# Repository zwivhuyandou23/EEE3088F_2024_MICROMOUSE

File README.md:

# Welcome to the EEE3088F_2024_MICROMOUSE hardware project

## Name
 2024 Micromouse Project

## Description
The Micromouse Project is a maze-solving robot project designed for the EEE3088F 2024 course. Students will focus on designing and manufacturing sensor and power modules for the micro-mouse, meeting specific project requirements while adhering to a strict budget.

## Features
- Sensor module for detecting obstacles
- Power module for powering the entire system
- Integration with provided motherboard and processor boards

## Project Scenarios
Maze completion.

## Usage
The Micromouse project is intended for educational purposes in the EEE3088F 2024 course. Zwivhuya Ndou and Innocent Makhubela worked on designing, manufacturing, and demonstrating the sensor and power modules for the micro-mouse robot.

## Installation
To access some of the contents on the repo you will need kicad to open the project PCB, Schematics designs and an IDE that supports C programming

## Authors and acknowledgment
Zwivhuya Ndou, Innocent Makhubela

## Contributing

Contributions to the ENVIRO-SENSING-HAT project are welcome! If you have any ideas, bug fixes, or improvements, please follow the guidelines outlined in the [CONTRIBUTING.md](CONTRIBUTING.md) file.

## License

The ENVIRO-SENSING-HAT project is licensed under the MIT License. See the [LICENSE](LICENSE.md) file for more information.

## Project status
Ongoing - part of the EEE3088F 2024 course project, to be carried to the second semester course.

## Contact
If you have any questions or inquiries about the Micromouse project, feel free to contact us at Zwivhuya Ndou(ndxzwi002@myuct.ac.za), Innocent Makhubela ().

Thank you for your interest in the Micromouse project!

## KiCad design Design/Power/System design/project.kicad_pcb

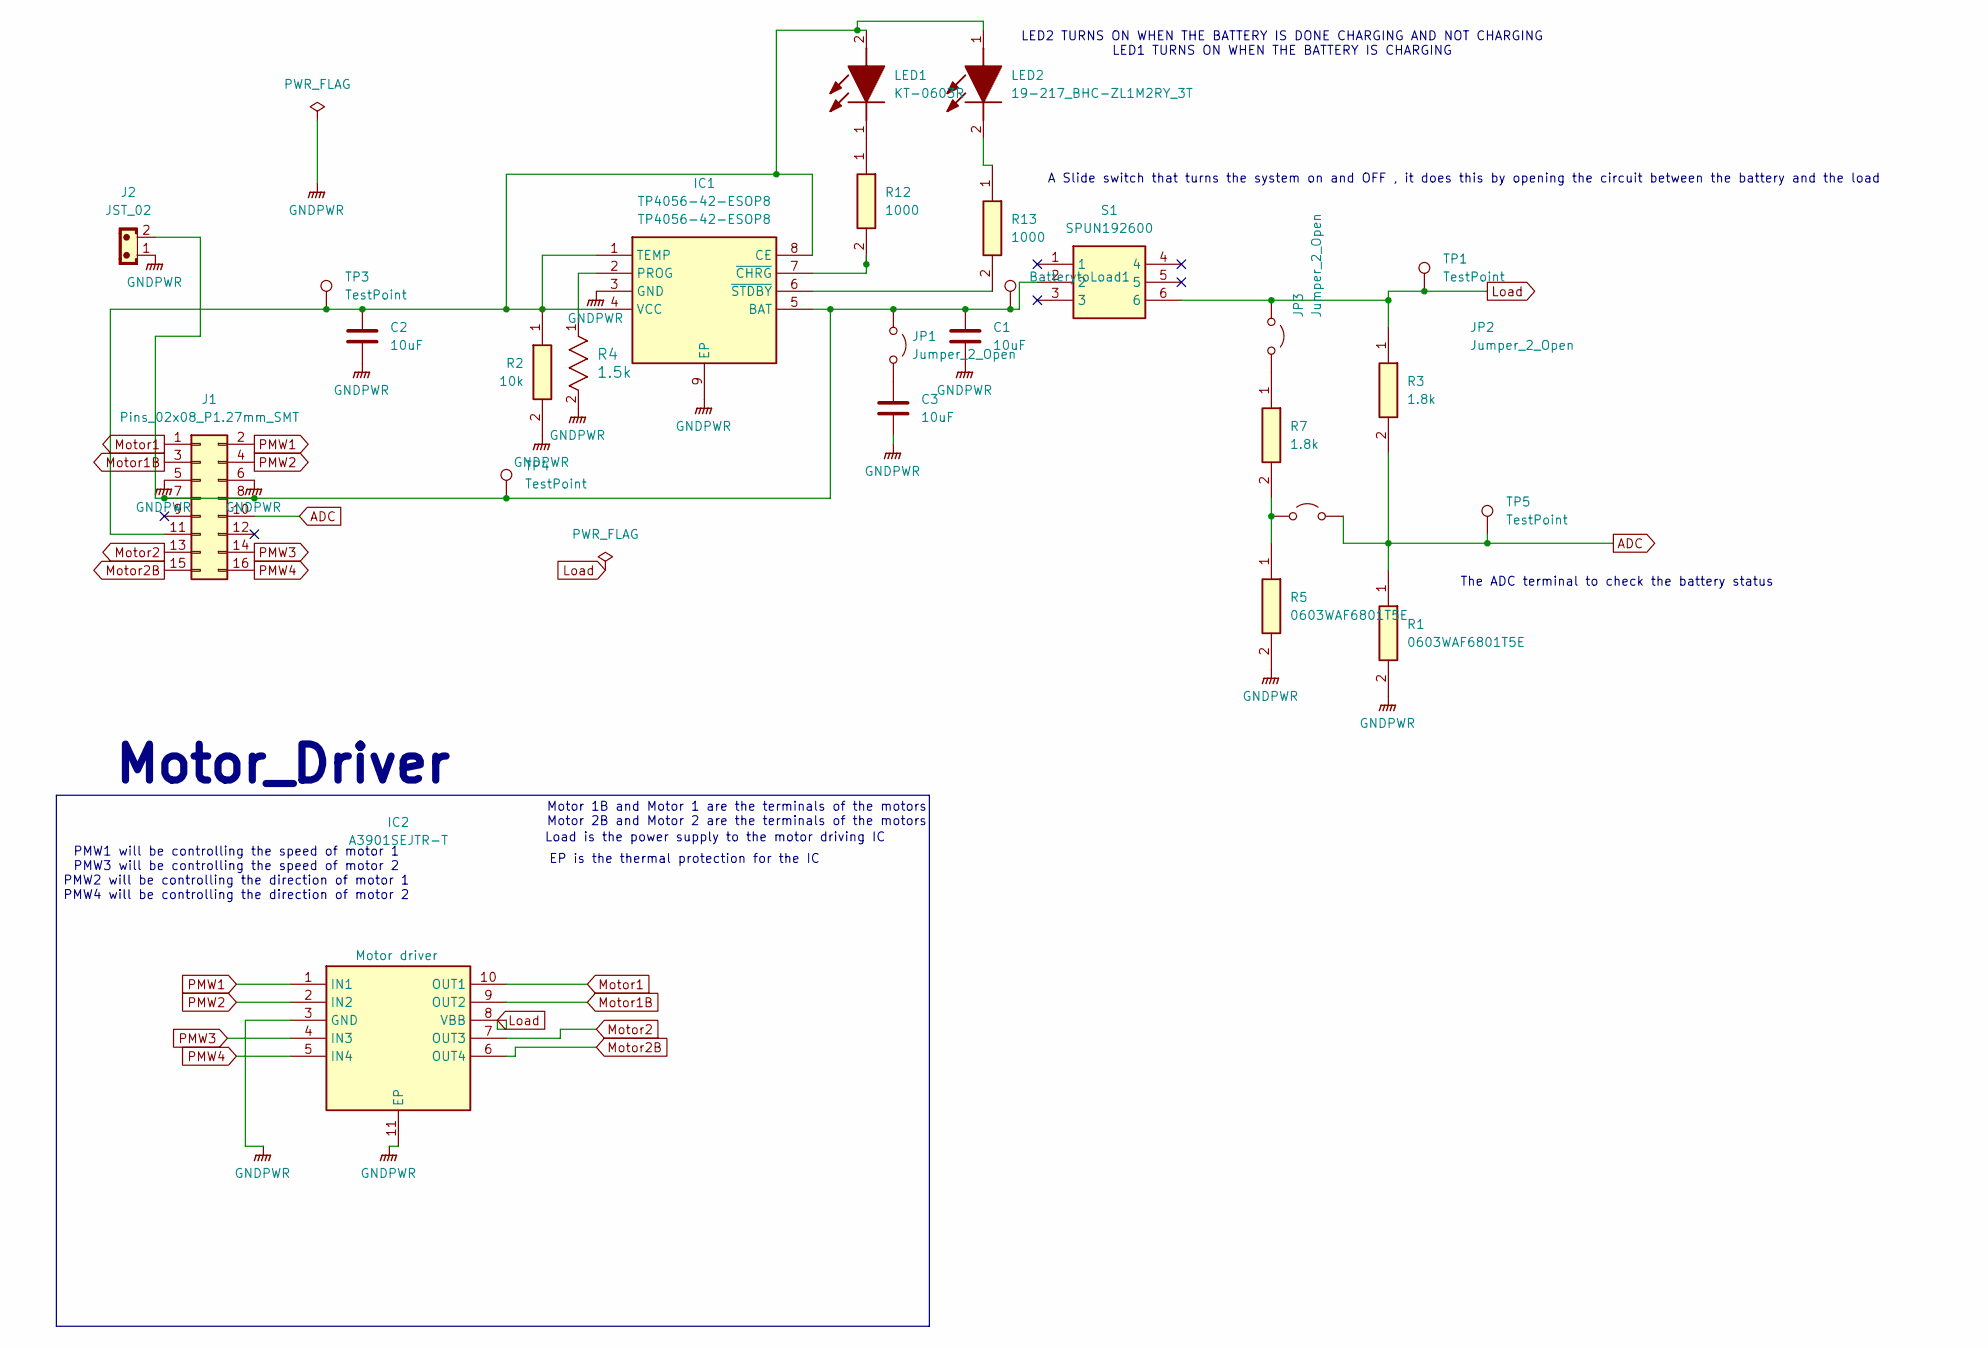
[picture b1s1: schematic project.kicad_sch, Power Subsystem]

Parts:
BatterytoLoad1: TestPoint; TestPoint_Pad_04
C1, C2, C3: 10uF; CAPC1005X70N
IC1: TP4056-42-ESOP8; SOIC127P600X175-9N; Manufacturer_Part_Number TP4056-42-ESOP8
IC2: A3901SEJTR-T; SON50P300X300X75-11N-D; Manufacturer_Part_Number A3901SEJTR-T; Mouser Part Number Motor driver
J1: Pins_02x08_P1.27mm_SMT; PinHeader_2x08_P2.54mm_Vertical; Part Number FTSH-108-01-F-DV
J2: JST_02; JST_JWPF_B02B-JWPF-SK-R_1x02_P2.00mm_Vertical
JP1, JP2, JP3: Jumper_2_Open; SolderJumper-2_P1.3mm_Open_RoundedPad1.0x1.5mm
LED1: KT-0603R; LEDC1608X70N; Manufacturer_Part_Number KT-0603R
LED2: 19-217_BHC-ZL1M2RY_3T; 19217BHCZL1M2RY3T; Manufacturer_Part_Number 19-217/BHC-ZL1M2RY/3T
R1, R5: 0603WAF6801T5E; RESC1608X55N; Manufacturer_Part_Number 0603WAF6801T5E
R2: 10k; RESC3116X65N; Manufacturer_Part_Number 1206W4F1002T5E
R3, R7: 1.8k; RESC1608X55N; Manufacturer_Part_Number 0603WAF1801T5E
R4: 1.5k; RES_8F1001T5E_UNR
R12: 1000; RESC1608X55N; Manufacturer_Part_Number 0603WAF1001T5E
R13: 1000; SOT95P280X145-5N; Manufacturer_Part_Number 0603WAF1001T5E
S1: SPUN192600; Manufacturer_Part_Number SPUN192600; Mouser Part Number 688-SPUN192600
TP1, TP3, TP4, TP5: TestPoint; TestPoint_Pad_04

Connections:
ADC: J1.10 (GND), JP3.2 (B), R1.1, R3.2, TP5.1; also elsewhere on the board
GNDPWR: C1.2, C2.2, C3.2, IC1.3 (GND), IC1.9 (EP), IC2.3 (GND), IC2.11 (EP), J1.5 (+12V), J1.6, J2.1, R1.2, R2.2, R4.2, R5.2
Load: IC2.8 (VBB), JP2.1 (A), R3.1, S1.6, TP1.1
Motor1: IC2.10 (OUT1), J1.1
Motor1B: IC2.9 (OUT2), J1.3
Motor2: IC2.7 (OUT3), J1.13 (-12)
Motor2B: IC2.6 (OUT4), J1.15 (-12V)
unnamed: BatterytoLoad1.1, C1.1, IC1.5 (BAT), J1.7 (12V), J1.8 (+12V), J2.2, JP1.1 (A), S1.2, TP4.1
unnamed 8: C2.1, IC1.1 (TEMP), IC1.4 (VCC), IC1.8 (CE), J1.11 (GND), LED1.2 (A), LED2.1 (A), R2.1, TP3.1; also elsewhere on the board
unnamed: IC1.2 (PROG), R4.1
unnamed: IC1.7 (~CHRG), R12.2
unnamed: IC1.6 (~STDBY), R13.2
unnamed: C3.1, JP1.2 (B)
unnamed: JP2.2 (B), R7.1
unnamed: JP3.1 (A), R5.1, R7.2
unnamed: LED1.1 (K), R12.1
unnamed: LED2.2 (K), R13.1
PMW1: IC2.1 (IN1), J1.2
PMW2: IC2.2 (IN2), J1.4
PMW3: IC2.4 (IN3), J1.14 (-12V)
PMW4: IC2.5 (IN4), J1.16

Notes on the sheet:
Motor 1B and Motor 1 are the terminals of the motors
PMW1 will be controlling the speed of motor 1 PMW3 will be controlling the speed of motor 2 PMW2 will be controlling the direction of motor 1 PMW4 will be controlling the direction of motor 2
The ADC terminal to check the battery status
Motor_Driver
Motor 2B and Motor 2 are the terminals of the motors
Load is the power supply to the motor driving IC
LED2 TURNS ON WHEN THE BATTERY IS DONE CHARGING AND NOT CHARGING LED1 TURNS ON WHEN THE BATTERY IS CHARGING
A Slide switch that turns the system on and OFF , it does this by opening the circuit between the battery and the load
EP is the thermal protection for the IC

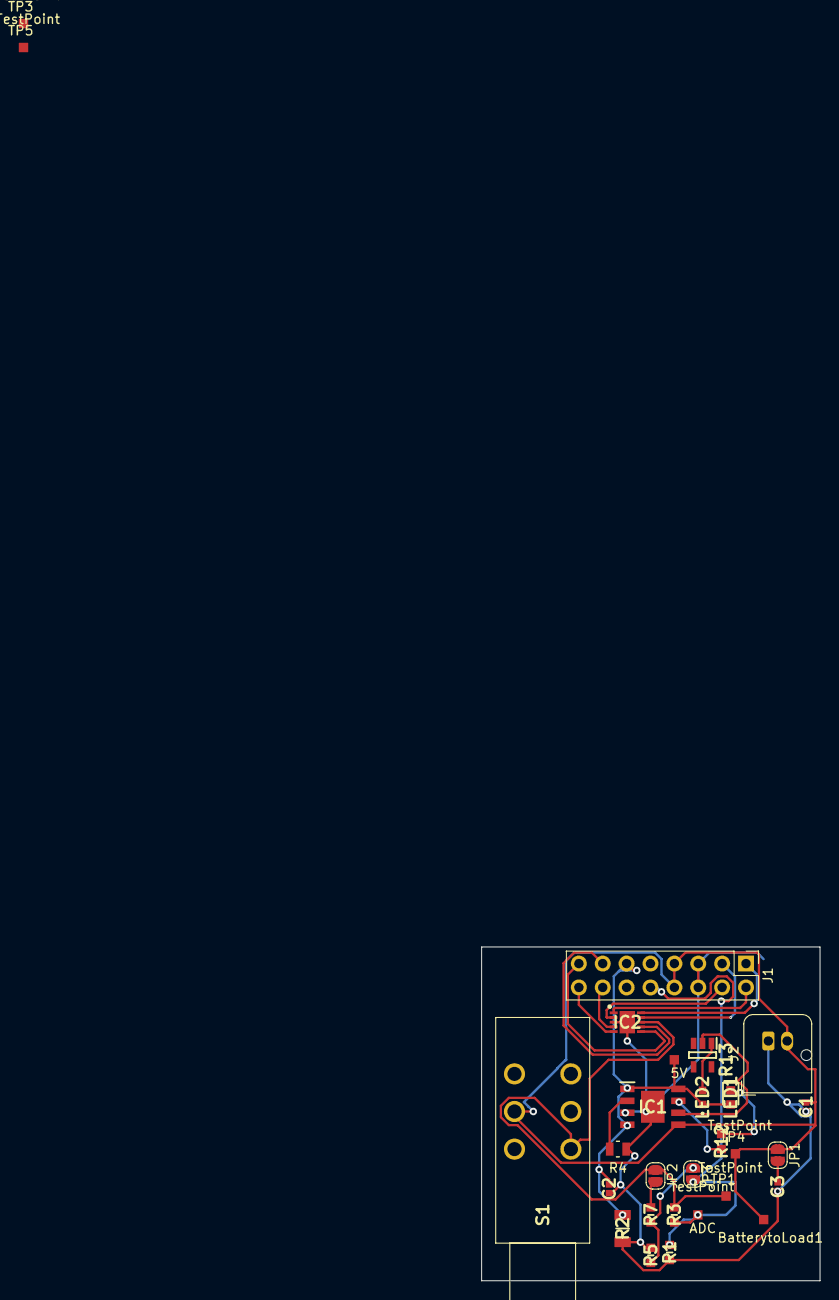
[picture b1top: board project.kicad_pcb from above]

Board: 2 copper layers, 36.0 x 35.5 mm, 28 parts (0 on the bottom side), 21 nets.

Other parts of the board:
5V: TestPoint; TestPoint_Pad_04
ADC: TestPoint; TestPoint_Pad_04

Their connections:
ADC: ADC.1; also elsewhere on the board
unnamed 8: 5V.1; also elsewhere on the board

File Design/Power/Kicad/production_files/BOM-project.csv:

Comment,Designator,Footprint,LCSC;
SPUN192600,S1,SPUN192600,;
A3901SEJTR-T,IC2,SON50P300X300X75-11N-D,;
19-217_BHC-ZL1M2RY_3T,LED2,19217BHCZL1M2RY3T,;
KT-0603R,LED1,LEDC1608X70N,;
TP4056-42-ESOP8,IC1,SOIC127P600X175-9N,;
1000,R13,0603WAF1001TSE,;0603WAF1001TSE,
1000,R12,0603WAF1001TSE,;0603WAF1001TSE,
1.5k,R4,RES_8F1001T5E_UNR,;
0603WAF6801T5E,R5,RESC1608X55N,;
10uF,C2,CAPC1005X70N,;
1.8k,R7,RESC1608X55N,;
10uF,C3,CAPC1005X70N,;
10uF,C1,CAPC1005X70N,;
1.8k,R3,RESC1608X55N,;
10k,R2,RESC3116X65N,;
0603WAF6801T5E,R1,RESC1608X55N,;

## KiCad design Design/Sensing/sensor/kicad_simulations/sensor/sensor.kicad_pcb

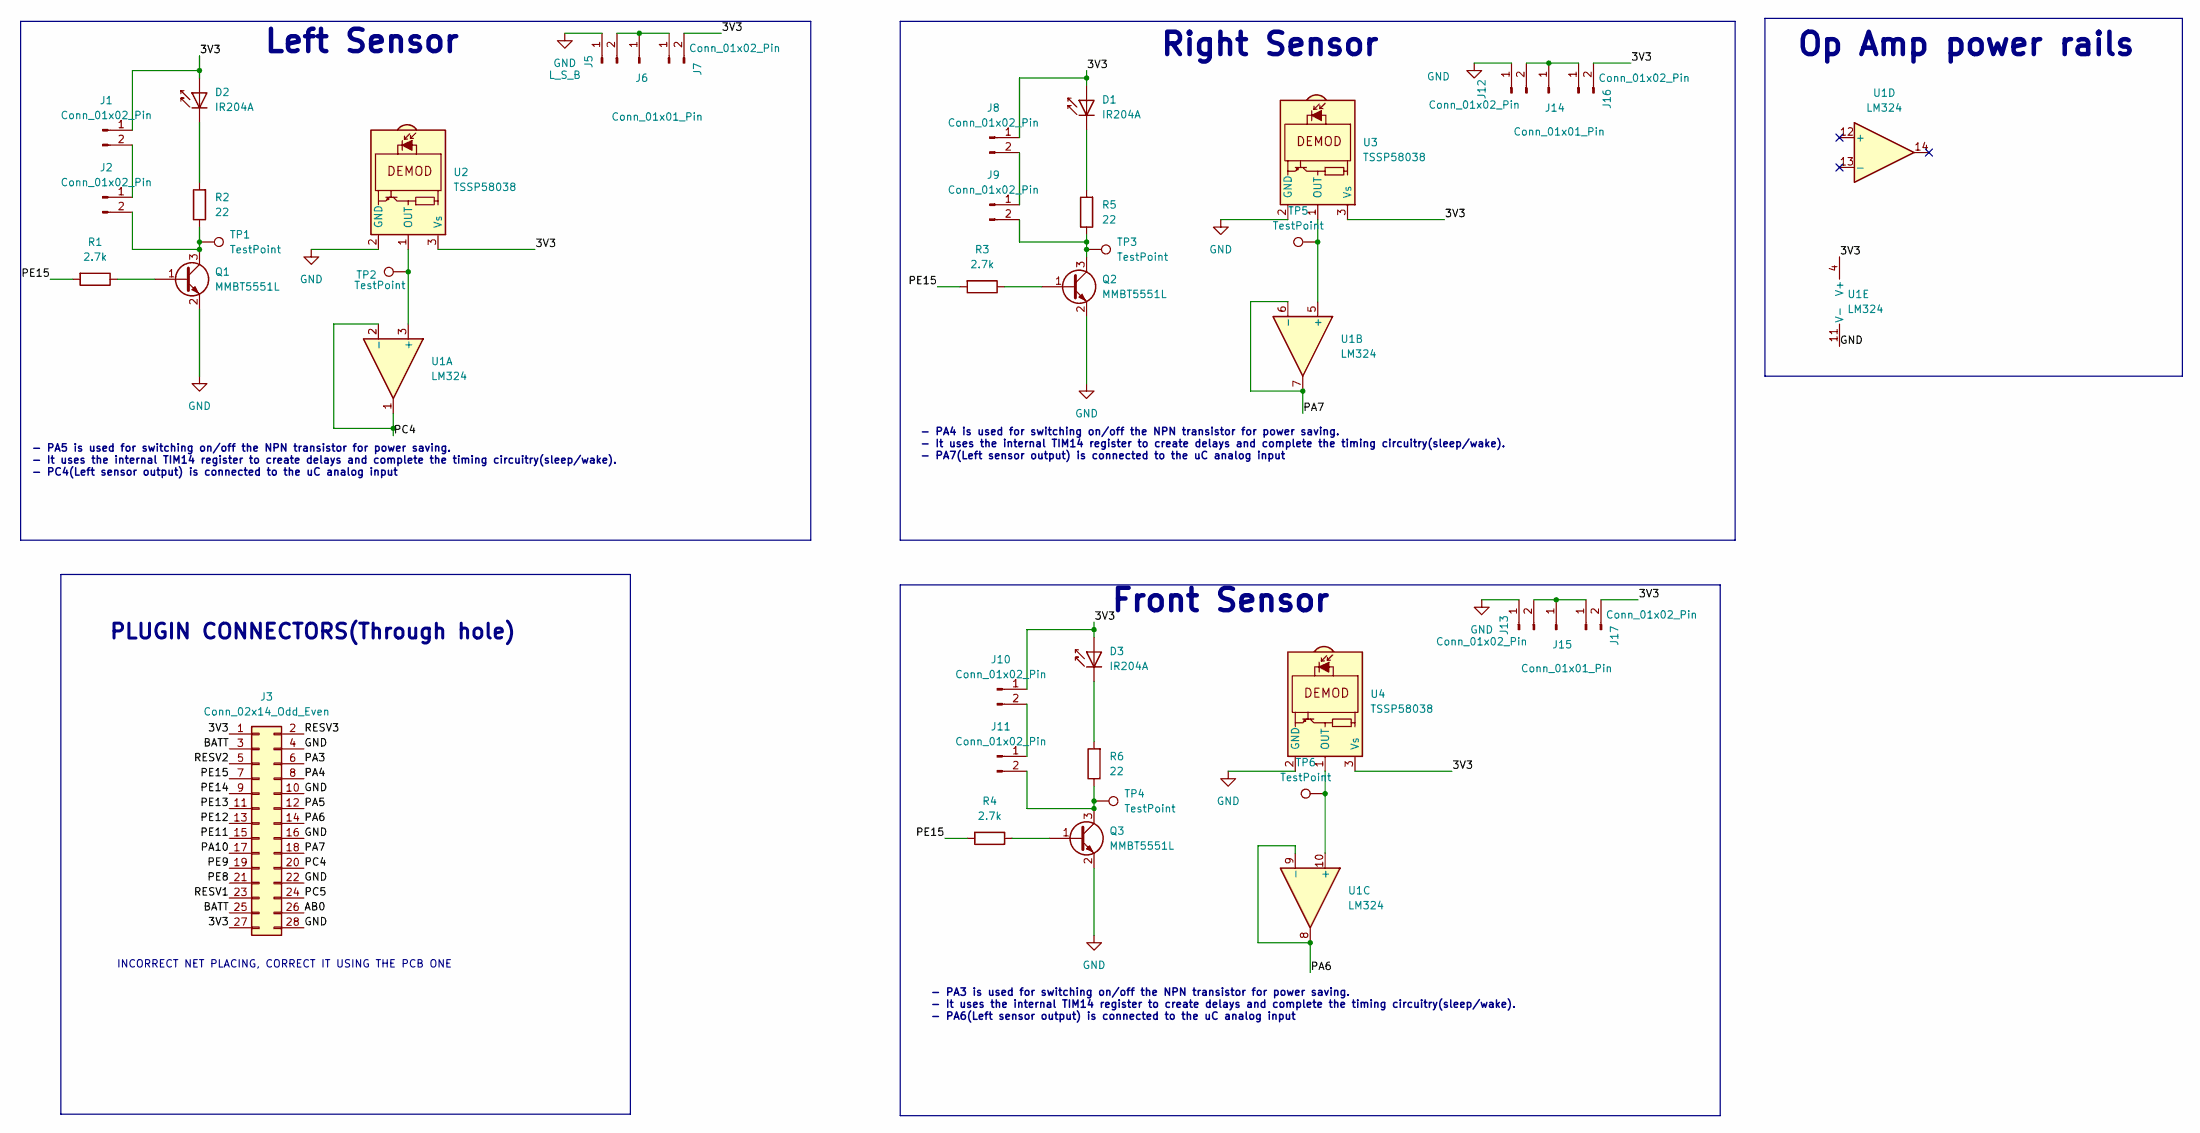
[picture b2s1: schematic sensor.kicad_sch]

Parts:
D1, D2, D3: IR204A; LED_D3.0mm_Horizontal_O1.27mm_Z2.0mm_IRBlack
J1, J2, J7, J8, J9, J10, J11, J12, J13, J16, J17: Conn_01x02_Pin; PinHeader_1x02_P2.54mm_Vertical
J3: Conn_02x14_Odd_Even; PinHeader_2x14_P2.54mm_Vertical
J5: L_S_B; PinHeader_1x02_P2.54mm_Vertical
J6, J14, J15: Conn_01x01_Pin; PinHeader_1x01_P2.54mm_Vertical
Q1, Q2, Q3: MMBT5551L; SOT-23
R1, R3, R4: 2.7k; R_0805_2012Metric
R2, R5, R6: 22; R_0805_2012Metric
TP1, TP2, TP3, TP4, TP5, TP6: TestPoint; TestPoint_Pad_D1.0mm
U1: LM324; SOIC-14_3.9x8.7mm_P1.27mm
U2, U3, U4: TSSP58038; Vishay_MINICAST-3Pin

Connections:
/3V3: D1.2 (A), D2.2 (A), D3.2 (A), J1.1, J3.1, J3.27, J7.2, J8.1, J10.1, J16.2, J17.2, U1.4 (V+), U2.3 (Vs), U3.3 (Vs), U4.3 (Vs)
/AB0: J3.26
/BATT: J3.3, J3.25
/PA3: J3.6
/PA4: J3.8
/PA5: J3.12
/PA6: J3.14, U1.8, U1.9 (-)
/PA7: J3.18, U1.6 (-), U1.7
/PA10: J3.17
/PC4: J3.20, U1.1, U1.2 (-)
/PC5: J3.24
/PE8: J3.21
/PE9: J3.19
/PE11: J3.15
/PE12: J3.13
/PE13: J3.11
/PE14: J3.9
/PE15: J3.7, R1.2, R3.2, R4.2
/RESV1: J3.23
/RESV2: J3.5
/RESV3: J3.2
GND: J3.4, J3.10, J3.16, J3.22, J3.28, J5.1, J12.1, J13.1, Q1.2 (E), Q2.2 (E), Q3.2 (E), U1.11 (V-), U2.2 (GND), U3.2 (GND), U4.2 (GND)
unnamed: D1.1 (K), R5.2
unnamed: D2.1 (K), R2.2
unnamed: D3.1 (K), R6.2
unnamed: J1.2, J2.1
unnamed: J2.2, Q1.3 (C), R2.1, TP1.1
unnamed: J5.2, J6.1, J7.1
unnamed: J8.2, J9.1
unnamed: J9.2, Q2.3 (C), R5.1, TP3.1
unnamed: J10.2, J11.1
unnamed: J11.2, Q3.3 (C), R6.1, TP4.1
unnamed: J12.2, J14.1, J16.1
unnamed: J13.2, J15.1, J17.1
unnamed: Q1.1 (B), R1.1
unnamed: Q2.1 (B), R3.1
unnamed: Q3.1 (B), R4.1
unnamed: TP2.1, U1.3 (+), U2.1 (OUT)
unnamed: TP5.1, U1.5 (+), U3.1 (OUT)
unnamed: TP6.1, U1.10 (+), U4.1 (OUT)

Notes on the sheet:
- PA5 is used for switching on/off the NPN transistor for power saving. - It uses the internal TIM14 register to create delays and complete the timing circuitry(sleep/wake). - PC4(Left sensor output) is connected to the uC analog input
- PA4 is used for switching on/off the NPN transistor for power saving. - It uses the internal TIM14 register to create delays and complete the timing circuitry(sleep/wake). - PA7(Left sensor output) is connected to the uC analog input
Op Amp power rails
- PA3 is used for switching on/off the NPN transistor for power saving. - It uses the internal TIM14 register to create delays and complete the timing circuitry(sleep/wake). - PA6(Left sensor output) is connected to the uC analog input
Left Sensor
PLUGIN CONNECTORS(Through hole)
Front Sensor
INCORRECT NET PLACING, CORRECT IT USING THE PCB ONE
Right Sensor

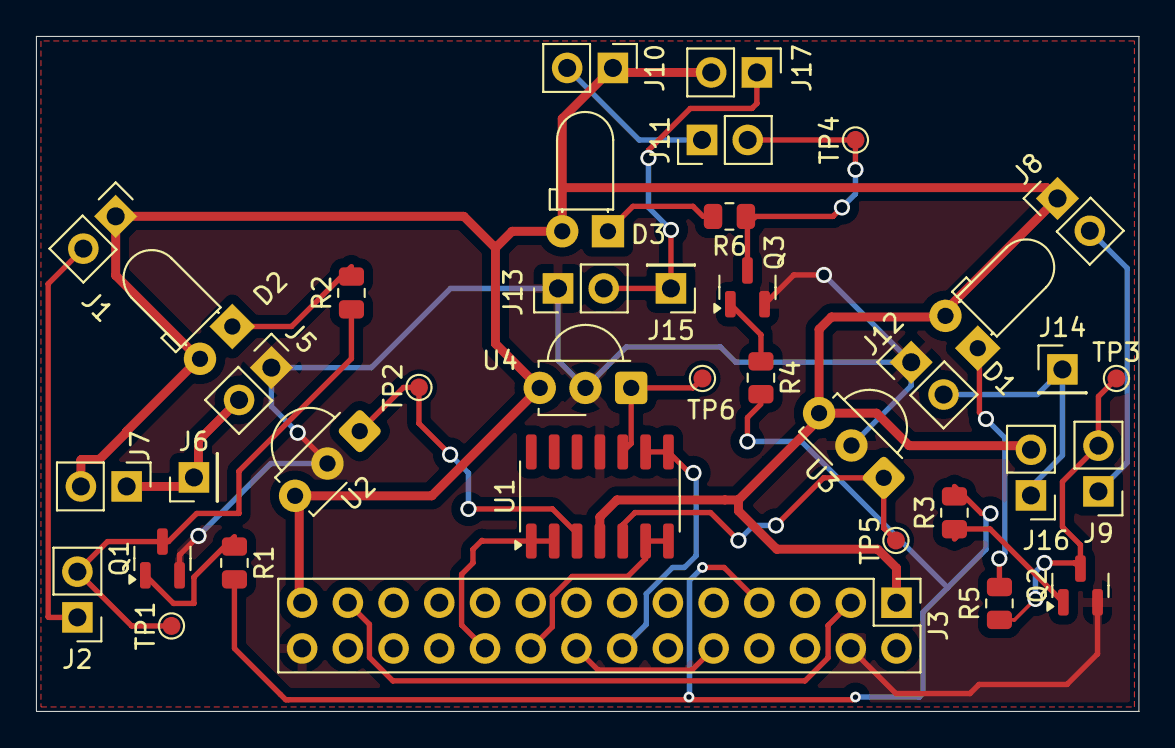
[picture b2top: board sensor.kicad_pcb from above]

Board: 2 copper layers, 61.2 x 37.5 mm, 38 parts (0 on the bottom side), 25 nets.

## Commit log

2024-03-19 Folders for Power and Sensing created for each subsytem's files
2024-03-19 Repo created and necessary folders created
2024-03-19 Added new schematic
2024-03-19 Resistor values for emitter circuit done, still have to name the circuits properly
2024-03-21 Sensing schematics done, the next stage is working on pcb component placement
2024-03-21 Footprints assigned
2024-03-21 All Footprints assigned
2024-03-21 PCB components placed but unrooted
2024-03-22 working on pcb
2024-03-22 PCB placement done, now need to root/make track connections
2024-03-22 PCB track done but still have 23 unrouted
2024-03-22 Only two unrouted and 3 errors remaining
2024-03-22 pcb placement redo
2024-03-24 Routed correct design
2024-03-24 Gerber files generated
2024-03-24 IR change
2024-03-24 Added
2024-03-24 new sensor
2024-03-24 Trace length sorted
2024-03-24 gerber files generated, pcb quote 8 in total and under the budget
2024-03-24 Gerber files done
2024-03-24 ensured that net names in the connectors matches the label in th project
2024-03-24 Final gerber files generated
2024-03-24 Gerbers due for submission
2024-03-24 All project deliverables submitted
2024-04-02 Create Power
2024-04-02 Rename Power to Design/Power
2024-04-02 Rename Design/Power to Design/Power /EEE3088F_2024_project_description_v5.pdf
2024-04-02 The main project description
2024-04-02 Create Schematic
2024-04-02 The schematic of the subsystem without description
2024-04-02 a Folder with the summary of the designing procedures/proceses
2024-04-02 Rename Design/Power/System design to Design/Power/System design /dumbfile.pdf
    ignore the file (used to create a folder
2024-04-06 Create specs and requirements
2024-04-06 Update specs and requirements
2024-04-06 Add files via upload
    the draft context diagram of the subsystem
2024-04-06 Add files via upload
    the draft of the context diagram
2024-04-06 Add files via upload
    All the KICAD FILES FOR THE PROJECT
2024-04-06 Delete Design/Power/System design directory
    the directory is a duplicste
2024-04-06 Delete Design/Power/System design directory
    duplicate file
2024-04-08 Update README.md
    Trying out out play with read.me
2024-04-16 Docs folder created
2024-04-16 Trying to make the repo clean
2024-04-19 Updated the schematic
2024-04-19 Updated the schematicgit
2024-04-26 Libraries for demo updated
2024-05-14 Code Project for Sensing Visualisation
2024-05-14 Sensor Design Completed
2024-05-14 Project test results
2024-05-14 Project Code
2024-05-14 Add files via upload
    Project Documents
2024-05-14 Project Documents
